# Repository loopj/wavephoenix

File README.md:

<h1 align="center">
    WavePhoenix
</h1>

<p align="center">
    Open-source implementation of the Nintendo WaveBird receiver using Silicon Labs Wireless Gecko SoCs
</p>
<p align="center">
    
</p>

## Motivation

The WaveBird controller is, in my opinion, one of the best controllers ever made. It is wireless, has an insane battery life, and is very comfortable to hold. The WaveBird set a new standard for wireless controllers. It was the first major console controller to use radio frequency (RF) technology, providing a reliable, lag-free connection that didn't require line-of-sight, unlike infrared controllers.

Unfortunately, Nintendo stopped producing the WaveBird more than a decade ago, causing a dwindling supply of controllers and, especially, receivers. Given the decreasing supply of receivers and the increasing resale prices, I decided to design my own from scratch.

## Features

The reference implementation of WavePhoenix includes the following features:

- Full compatibility with the original WaveBird controller
- One-button virtual pairing, like modern wireless devices
- Status LED to indicate pairing status and radio activity
- Over-the-air firmware updates via Bluetooth
- Open source hardware and firmware
- 3D printable case

## Buying a WavePhoenix

Don't want to build your own? A number of vendors are now selling pre-assembled WavePhoenix receivers!

- [Laser Bear Industries](https://www.laserbear.net/products/wavephoenix-replacement-wavebird-gamecube-receiver) - US-based seller, custom enclosure and PCB by Greg
- [Colester Productions](https://shop.colesterproductions.com/product/wave-phoenix) - US-based seller, uses my original PCB and [
SadSnifit's fantastic case](https://makerworld.com/en/models/1463984-wavephoenix-wavebird-shell)
- [Various AliExpress sellers](https://www.aliexpress.us/w/wholesale-%22wavephoenix%22.html)

## Building a WavePhoenix

The bare minimum hardware needed to build a WavePhoenix is a EFR32BG22 radio module (such as the [RF-BM-BG22C3](https://www.rfstariot.com/rf-bm-bg22c3-efr32bg22-bluetooth-module_p93.html)), a GameCube controller connector, and 3 wires!

Since most people prefer a more streamlined solution, I designed a custom PCB and 3D-printable case called the *Mini Receiver*.

You can find detailed build instructions in the [hardware/mini-receiver](hardware/mini-receiver) directory.

## Firmware Components

The firmware for WavePhoenix is composed of the following components:

- [`libwavebird`](https://github.com/loopj/libwavebird) - my implementation of Nintendo's WaveBird protocol for Silicon Labs Gecko SoCs
- [`libjoybus`](https://github.com/loopj/libjoybus) - my implementation of the Joybus protocol used by N64 and GameCube controllers
- [`firmware/app`](firmware/app) - the main app firmware; a reference implementation of a WaveBird receiver
- [`firmware/bootloader`](firmware/bootloader) - bootloader to provide over-the-air firmware updates via Bluetooth

## Worklog

Check out the [worklog](WORKLOG.md) for a detailed history of the development of the WavePhoenix project.

## Special Thanks

- [Sam Edwards](https://github.com/CFSworks) for his incredible WaveBird reverse engineering documentation, which was essential in getting this working
- [Jeff Longo](https://jefflongo.dev) - for his detailed GameCube controller protocol documentation
- [Aurelio Mannara](https://github.com/Aurelio92) - for open sourcing GC+, another great reference for the GameCube controller protocol
- [YveltalGriffin](https://bsky.app/profile/mks.bsky.social) - for help and advice along the way, and helping me figure out those mysterious origin packets
- piotref1 - for being the very first person to build a WavePhoenix receiver and provide feedback, a true early adopter!
- Everyone in the incredible [BitBuilt community](https://bitbuilt.net/) for their support and encouragement throughout this project

## License

WavePhoenix is a permissively licensed open source project.

The firmware is licensed under the [MIT License](firmware/LICENSE).

The hardware is licensed under the [Solderpad Hardware License v2.1](hardware/LICENSE).

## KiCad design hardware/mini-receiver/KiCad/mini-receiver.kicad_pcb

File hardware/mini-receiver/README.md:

# WavePhoenix Mini Receiver

The WavePhoenix Mini Receiver is a small, low-cost WaveBird receiver replacement. It has been designed to be as cheap as possible (~$4 in parts) and simple to build.

The receiver uses a cheap, off-the-shelf wireless module (the [RF-BM-BG22C3](https://www.rfstariot.com/rf-bm-bg22c3-efr32bg22-bluetooth-module_p93.html)), which can either be hand-wired, or assembled onto a custom PCB.

## Build Guide

### Parts

- Assembled Mini Receiver PCB - (see [PCB](#pcb))
- 3D printed case - (see [Case](#case))
- GameCube male connector - ([AliExpress](https://www.aliexpress.us/item/3256804501860592.html), [Alibaba](https://www.alibaba.com/product-detail/NGC-Gamecube-Male-Connector_1600107604838.html), [eBay](https://www.ebay.com/itm/354372477064))
- JST-SH 4-Pin connector with pre-crimped cable - ([AliExpress](https://www.aliexpress.us/item/3256803952186380.html), [Amazon](https://www.amazon.com/dp/B0D9WMLZ7B/))
- 1.5mm PMMA fiber cable - ([AliExpress](https://www.aliexpress.us/item/3256806278563564.html)) *or* 1.5mm diameter x 4mm light pipe - ([AliExpress](https://www.aliexpress.us/item/3256801194682892.html))
- Crimping tool or soldering iron (depending on the your connector type)

### Assembly

- Assemble the JST-SH to GameCube connector cable - (see [Cable](#cable))
- Flash the firmware - (see [Initial Firmware Flashing](#initial-firmware-flashing))
- Insert the GameCube connector into the case until it clicks into place
- Connect the JST-SH connector to the PCB
- Insert the PCB into the case, ensuring the LED and switch are aligned with the holes in the case, it should click into place
- Insert the light pipe into the small hole in the front of the case, if using PMMA fiber for the light pipe, cut it to size first (4mm)
- Insert the 3D printed button into the large hole in the front of the case
- Press the front of the case onto the back of the case

## PCB

The WavePhoenix Mini Receiver PCB is a simple carrier PCB for a RF-BM-BG22C3 module, tact switch, status LED, and a connector for the GameCube controller port.

### Ordering from JLCPCB, PCBWay, etc

You can find the gerber files in the [`gerbers`](gerbers) directory.

Order the PCB with the following settings:

- 2-layer board
- PCB thickness of 1.2mm
- HASL is fine

### Bill of Materials

- 1x RF-BM-BG22C3 module ([AliExpress](https://www.aliexpress.us/item/3256804772492081.html), [LCSC](https://www.lcsc.com/product-detail/Bluetooth-Modules_RF-star-RF-BM-BG22C3_C5369196.html), [Tindie](https://www.tindie.com/products/rfstariot/small-size-efr32bg22-wireless-transceiver/))
- 1x 0805 green LED
- 1x 5x5mm tactile switch
- 1x 4-pin JST-SH connector
- 1x 0402 100Ω resistor (adjust as needed)
- 1x 0402 10uF capacitor
- 1x 0402 0.1uF capacitor

You can find a [Mouser shared cart here](https://www.mouser.com/ProjectManager/ProjectDetail.aspx?AccessID=66aed3ee61). You'll need to source the RF-BM-BG22C3 module separately.

You can find an [interactive BOM here](ibom.html).

### Hand Assembly

The components should all be hand solderable, the smallest parts being the 0402 capacitors and resistor. If you are struggling with the capacitors, you can omit them, but it is recommended to include them.

I recommend using magnification, and soldering the RF-BM-BG22C3 module first, since the module is hard to solder once the capacitors are in place.

### PCB Assembly Services

If you want to use a PCB assembly service such as JLC PCBA, the CPL file and the BOM file are also found in the [`gerbers`](gerbers) directory.

Unfortunately the RF-BM-BG22C3 module is not available for JLC's awesome economic assembly, so you will either need to pay for the standard assembly, or hand solder the module yourself.

## Case

I highly recommend you use [SadSnifit's WavePhoenix shell](https://makerworld.com/en/models/1463984-wavephoenix-wavebird-shell) for the case, it is very well designed and looks great.

Alternatively, my original 3D printable case for the receiver can be found in the [`case`](case) directory.

## Cable

> [!TIP]
> The [Fires Custom Controller](https://firescc.com/mod-guides#/diy-custom-cables) custom cable guide, covers the crimping the GameCube connector pins in detail!

Although we are using a 4-pin JST-SH connector, we only actually need 3 wires for the receiver. In the following photos, the ground wire is black, the power wire is red, and the data wire is blue, however the wire colors of pre-made JST cables vary *wildly*, so please check the pinout rather than relying on the wire colors in the photos.

Pin 1 on the JST-SH connector is indicated by a small triangle on the connector housing. In my photos below I have removed the unused wire from pin 4 of the JST-SH connector, but you can also leave it in place if you prefer.

First trim the wires on JST-SH connector cable to 30mm:

Strip a small amount of insulation (~1mm) off the ends of the wires, and crimp the wires to the GameCube connector pins.

Insert the crimped pins into the GameCube connector housing in the following positions:

The “wings” on each pin should face towards the center of the plug, and the pins should be inserted until they click into place.

Next we need to trim off and file down the cable retention tabs on the metal GameCube connector housing:

We can then finally insert the plastic connector into the metal housing:

The complete assembly should look like this:

## Initial Firmware Flashing

> [!NOTE]
> Once you have flashed the bootloader, you can use Bluetooth over-the-air updates to flash future firmware updates!

WavePhoenix receivers have two pieces of software running on them, the *bootloader* and the *application firmware*. The *bootloader* allows us to flash future application updates over Bluetooth, the *application firmware* is the program that handles WaveBird communication.

You can [find the latest bootloader and firmware here](https://github.com/loopj/wavephoenix/releases/latest), the mini-receiver needs the `rf-bm-bg22c3` build of the firmware.

The first-time flashing of the firmware requires a debug probe and some special software. If your WavePhoenix board already has the bootloader flashed, you can skip this part.

### Debug Probes

You'll need a SWD debug probe to flash the initial firmware onto the receiver. The debug probe connects to the receiver's SWD pins and allows you to flash the firmware using OpenOCD.

If you don't already have an SWD-capable debug probe, you can build one using a Raspberry Pi Pico. Instructions on how to build a debug probe using a Raspberry Pi Pico can be found in the [Appendix](#pi-pico-debug-probe).

### Pinouts

If you are flashing an assembled Mini Receiver board, the SWD pins are made available in two locations, pads on the back of the board, and via the 4-pin JST-SH connector.

The pinout of the JST-SH connector is as follows:

| Pin | Function | Description              |
| --- | -------- | ------------------------ |
| 1   | GND      | Ground                   |
| 2   | 3.3V     | Power                    |
| 3   | SWDIO    | SWD Data / GameCube Data |
| 4   | SWCLK    | SWD Clock                |

### OpenOCD

To flash the firmware, you'll need to install Arduino's fork of OpenOCD, which adds support for EFR32 Series 2 SoCs.

Prebuilt binaries are available for [Windows](https://downloads.arduino.cc/tools/openocd-0.12.0-arduino1-static-i686-w64-mingw32.tar.bz2), [macOS](https://downloads.arduino.cc/tools/openocd-0.12.0-arduino1-static-x86_64-apple-darwin19.tar.bz2), and [Linux](https://downloads.arduino.cc/tools/openocd-0.12.0-arduino1-static-x86_64-ubuntu16.04-linux-gnu.tar.bz2).

The source for this fork is available on [GitHub here](https://github.com/facchinm/OpenOCD/tree/arduino-0.12.0-rtx5).

### Flashing

Once you have OpenOCD installed, you can flash the bootloader and application firmware using the following commands:

#### Erase the device

First we'll need to do a full device erase:

```bash
# Linux / macOS
openocd -f "interface/cmsis-dap.cfg" \
        -f "target/efm32s2.cfg" \
        -c "init; efm32s2_dci_device_erase; shutdown"
```

```powershell
# Windows (PowerShell)
openocd.exe -f "interface\cmsis-dap.cfg" `
            -f "target\efm32s2.cfg" `
            -c "init; efm32s2_dci_device_erase; shutdown"
```

> [!IMPORTANT]  
> Disconnect then reconnect the debug probe to the receiver before proceeding to the next step.

#### Flash the bootloader

Then we can flash the bootloader:

```bash
# Linux / macOS
openocd -f "interface/cmsis-dap.cfg" \
        -c "transport select swd" \
        -f "target/efm32s2.cfg" \
        -c "init; halt; flash write_image erase bootloader.hex; exit"
```

```powershell
# Windows (PowerShell)
openocd.exe -f "interface\cmsis-dap.cfg" `
            -c "transport select swd" `
            -f "target\efm32s2.cfg" `
            -c "init; halt; flash write_image erase bootloader.hex; exit"
```

> [!TIP]  
> From this point on, you can now use Bluetooth over-the-air updates to flash new application firmware!

#### Flash the application

Since we already have the device wired up, we can also flash the receiver application using SWD:

```bash
# Linux / macOS
openocd -f interface/cmsis-dap.cfg \
        -c "transport select swd" \
        -f target/efm32s2.cfg \
        -c "init; halt; flash write_image erase receiver.hex; exit"
```

```powershell
# Windows
openocd.exe -f interface\cmsis-dap.cfg `
            -c "transport select swd" `
            -f target\efm32s2.cfg `
            -c "init; halt; flash write_image erase receiver.hex; exit"
```

You should now have a fully functional WavePhoenix receiver!

## Usage

### Pairing

WavePhoenix receivers use "virtual pairing" instead of the original WaveBird’s channel wheel. To initiate pairing, press the receiver’s pairing button. The onboard LED will start blinking to indicate the receiver is now in pairing mode. Press and hold X + Y on the WaveBird controller to pair a WaveBird to a receiver. Once pairing is successful, the LED will stop blinking and remain solid.

### Entering Bootloader Mode

You can enter the bootloader for OTA updates in two ways:

1. Press and hold the pairing button for more than 3 seconds, until the LED turns off
2. Press and hold the pairing button while plugging in the receiver

### Upgrading Firmware

You can always find the latest receiver firmware in the [latest release](https://github.com/loopj/wavephoenix/releases/latest) on GitHub. The firmware is available in two formats, a `.gbl` file for over-the-air updates, and a `.hex` file for flashing via SWD.

The mini receiver uses the `rf-bm-bg22c3` build of the firmware, which is specifically designed for the RF-BM-BG22C3 module.

#### Using WavePhoenix Web

If you have a computer with Bluetooth or an Android phone, you can use [WavePhoenix Web](https://web.wavephoenix.com) in Google Chrome to flash the firmware.

#### Flashing via SWD

You can also always use SWD to re-flash the firmware, as described in the [Initial Firmware Flashing](#initial-firmware-flashing) section.

## Appendix

### Pi Pico Debug Probe

If you have a Raspberry Pi Pico, you can use it as a debug probe to flash WavePhoenix firmware. The Pico is a low-cost (~$4) microcontroller board that can be used as a debug probe with OpenOCD.

Download the latest `debugprobe_on_pico.uf2` from the [Raspberry Pi Debug Probe repo](https://github.com/raspberrypi/debugprobe/releases/latest) and flash it to your Pico by dragging the file onto the Pico's USB drive. Once you have flashed the firmware, the Pico will now be available to use as a debug probe with OpenOCD.

Here's the pinout for SWD programming:

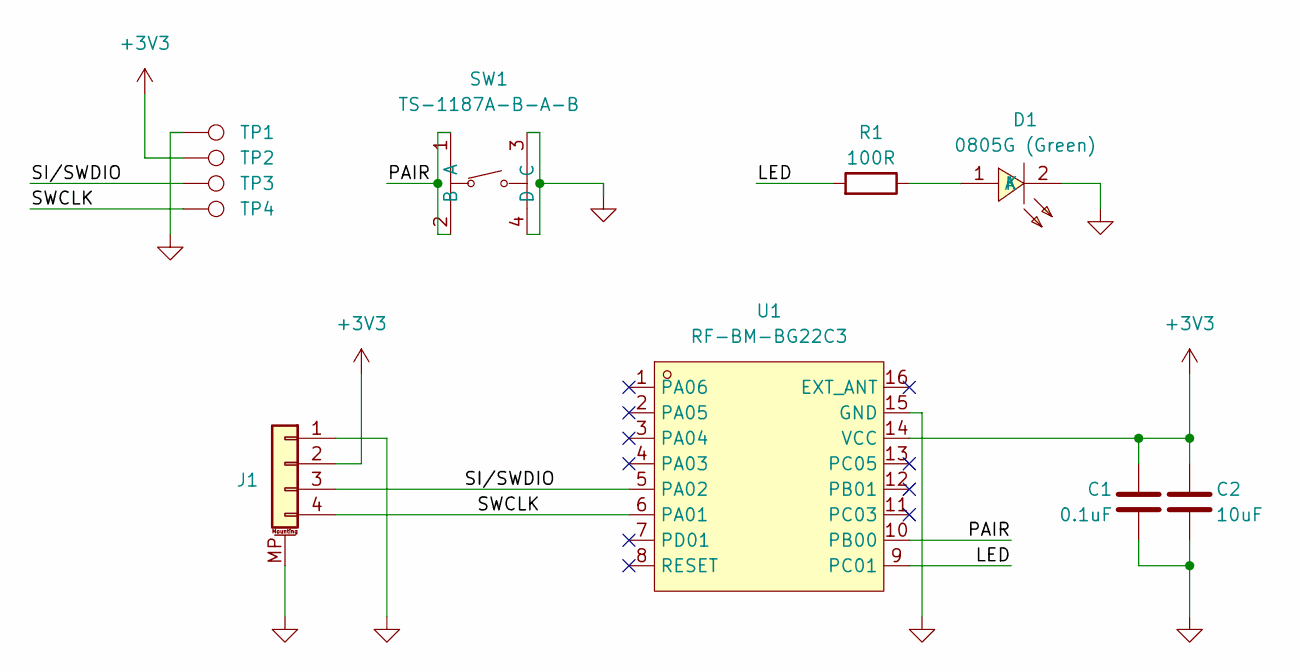
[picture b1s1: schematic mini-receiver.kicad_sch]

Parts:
C1: 0.1uF; C_0402_1005Metric; LCSC C1525
C2: 10uF; C_0402_1005Metric; LCSC C15525
D1: 0805G (Green); LED0805-R-RD; LCSC Part C2297
J1: Conn_01x04_MountingPin; JST_SH_SM04B-SRSS-TB_1x04-1MP_P1.00mm_Horizontal; LCSC C160404
R1: 100R; R_0402_1005Metric; LCSC C25076
SW1: TS-1187A-B-A-B; SW-SMD_4P-L5.1-W5.1-P3.70-LS6.5-TL-2; LCSC Part C318884
TP1: G; TestPoint_Pad_D1.0mm
TP2: V; TestPoint_Pad_D1.0mm
TP3: D; TestPoint_Pad_D1.0mm
TP4: C; TestPoint_Pad_D1.0mm
U1: RF-BM-BG22C3; WIFI-SMD_15P-P1.00-L8.0-W8.0-P1.00_RF-BM-BG22C3; LCSC C5369196

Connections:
+3V3: C1.1, C2.1, J1.2, TP2.1, U1.14 (VCC)
/LED: R1.2, U1.9 (PC01)
/PAIR: SW1.1 (A), SW1.2 (B), U1.10 (PB00)
/SI/SWDIO: J1.3, TP3.1, U1.5 (PA02)
/SWCLK: J1.4, TP4.1, U1.6 (PA01)
GND: C1.2, C2.2, D1.2 (K), J1.1, J1.MP (MountPin), SW1.3 (C), SW1.4 (D), TP1.1, U1.15 (GND)
unnamed: D1.1 (A), R1.1

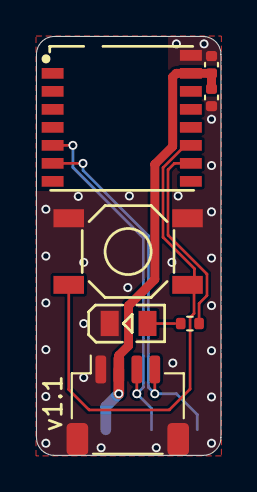
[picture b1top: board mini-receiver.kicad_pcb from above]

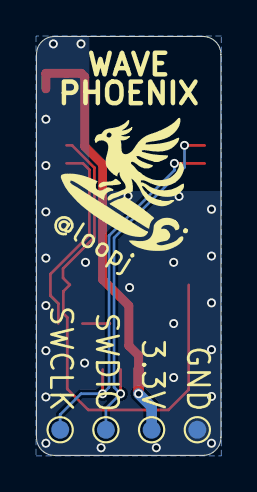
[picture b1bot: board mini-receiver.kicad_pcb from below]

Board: 2 copper layers, 10.2 x 23.3 mm, 11 parts (4 on the bottom side), 7 nets.

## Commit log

2025-04-25 Initial release
2025-04-25 Add license files
2025-04-25 Add special thanks section
2025-04-25 Update BOM links for GameCube male connector
2025-04-25 Point to the latest GitHub release in the build guide
2025-04-26 Quick note about entering bootloader mode
2025-04-27 Add link to WavePhoenix Web app
2025-04-27 Basic stubs for N64 controller support
2025-04-28 Factor out SI input/origin state updating
2025-04-29 Initial working N64 controller support, with hardcoded mappings
2025-06-30 WIP new module support on boards
2025-07-08 WIP serial output support
2025-07-09 Channel hopping support for pairing
2025-07-10 Add support for building libsi from zephyr
2025-07-10 Only require CONFIG_SOC_GECKO_USE_RAIL for libwavebird zephyr builds
2025-07-10 Recommend the Arduino fork of openocd instead of mine, since it has prebuilt binaries
2025-07-11 Rename the libsi efr32 driver
2025-07-14 Fix bootloader builds
2025-07-16 Use pre-defined LDMA structs for tx/rx
2025-07-16 Don't invert USART TX, use tristate instead
2025-07-21 WIP back to TIMER/PWM for pulse output, very fast callbacks, comparable start time
2025-08-01 Add support for enabling/disabling the radio to libwavebird
2025-08-01 Pull in additional emlib sources when building with Zephyr
2025-08-01 Connect zephyr IRQs
2025-08-02 libsi: automatic tx -> rx state transition
2025-08-02 libsi: Add peripheral selection support
2025-08-02 libsi: Rename input_valid function
2025-08-04 libsi: Reduce memory usage in command_table
2025-08-05 Refactor command handling
2025-08-05 Fix tests
2025-08-05 Fix auto tx->rx transition
2025-08-07 libsi: move gc specific si commands to gc_controller
2025-08-08 Remove complex bus state logic
2025-08-09 libsi: Add helper function to test if device is wireless
2025-08-11 Ensure need_origin flag is set correctly in both wired and wireless modes
2025-08-13 Add si_deinit function
2025-08-30 Move zephyr-specific build into zephyr module format
2025-09-10 Ignore all bootloader generated files
2025-09-10 Fix 'probe device' handling for launch window games
2025-09-10 Add test for probe_device changes
2025-09-12 Prepare version 0.9.3
2026-01-08 Drop cmake build wrapper, just use SLC
2026-01-08 Rail config generation script, add other configs
2026-01-08 Remove cmake remnants
2026-01-08 Working app properties/version
2026-01-08 Controller type string helper
2026-01-08 Configure clocks as they were previously
2026-01-09 Flatten firmware folder
2026-01-10 Remove libsi/libwavebird test running
2026-01-10 Remove internal libwavebird
2026-01-10 Add libwavebird as submodule
2026-01-10 Add build script
2026-01-10 Add libjoybus as submodule
2026-01-10 Port to libjoybus
2026-01-11 Re-work github action
2026-01-12 Share board configs between bootloader and app firmware, drop cmake
2026-01-12 Fix README links
2026-01-12 Remove deprecated firmware update methods
2026-01-14 Split out RF-BM-BG22C3 board config, define a Mini Receiver board
2026-01-15 Begin porting over local input from wavephoenix+
2026-03-24 Don't disable SWD immediately after flashing firmware
2026-03-24 Use nvm3 for settings
2026-03-24 Abstract out status LED to allow for different effects on future boards
2026-03-24 Drop channel wheel support
2026-03-24 Use sleeptimer for stale input validation
2026-03-24 Move libwavebird <-> libjoybus glue layer into own file
2026-03-24 Use new toggle_pairing function
